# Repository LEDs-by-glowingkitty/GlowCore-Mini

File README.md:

# GlowCoreMini

## Warning:

This project is currently under active development and has not been fully tested yet. If you decide to build or clone the project, be aware the project might not work yet as expected. Use at your own risk.

## What is this project?

A small PCB for controlling one LED strip. Program the integrated ESP32, and power everything via USB-C or DC power.

## Links

- [Schematic](https://github.com/glowingkitty/GlowCoreMini/blob/main/GlowCoreMini.pdf)
- [Interactive BOM](https://htmlpreview.github.io/?https://github.com/glowingkitty/GlowCoreMini/blob/main/bom/ibom.html)
- [PCB stencils](https://github.com/glowingkitty/GlowCoreMini/blob/main/PCB%20stencils)

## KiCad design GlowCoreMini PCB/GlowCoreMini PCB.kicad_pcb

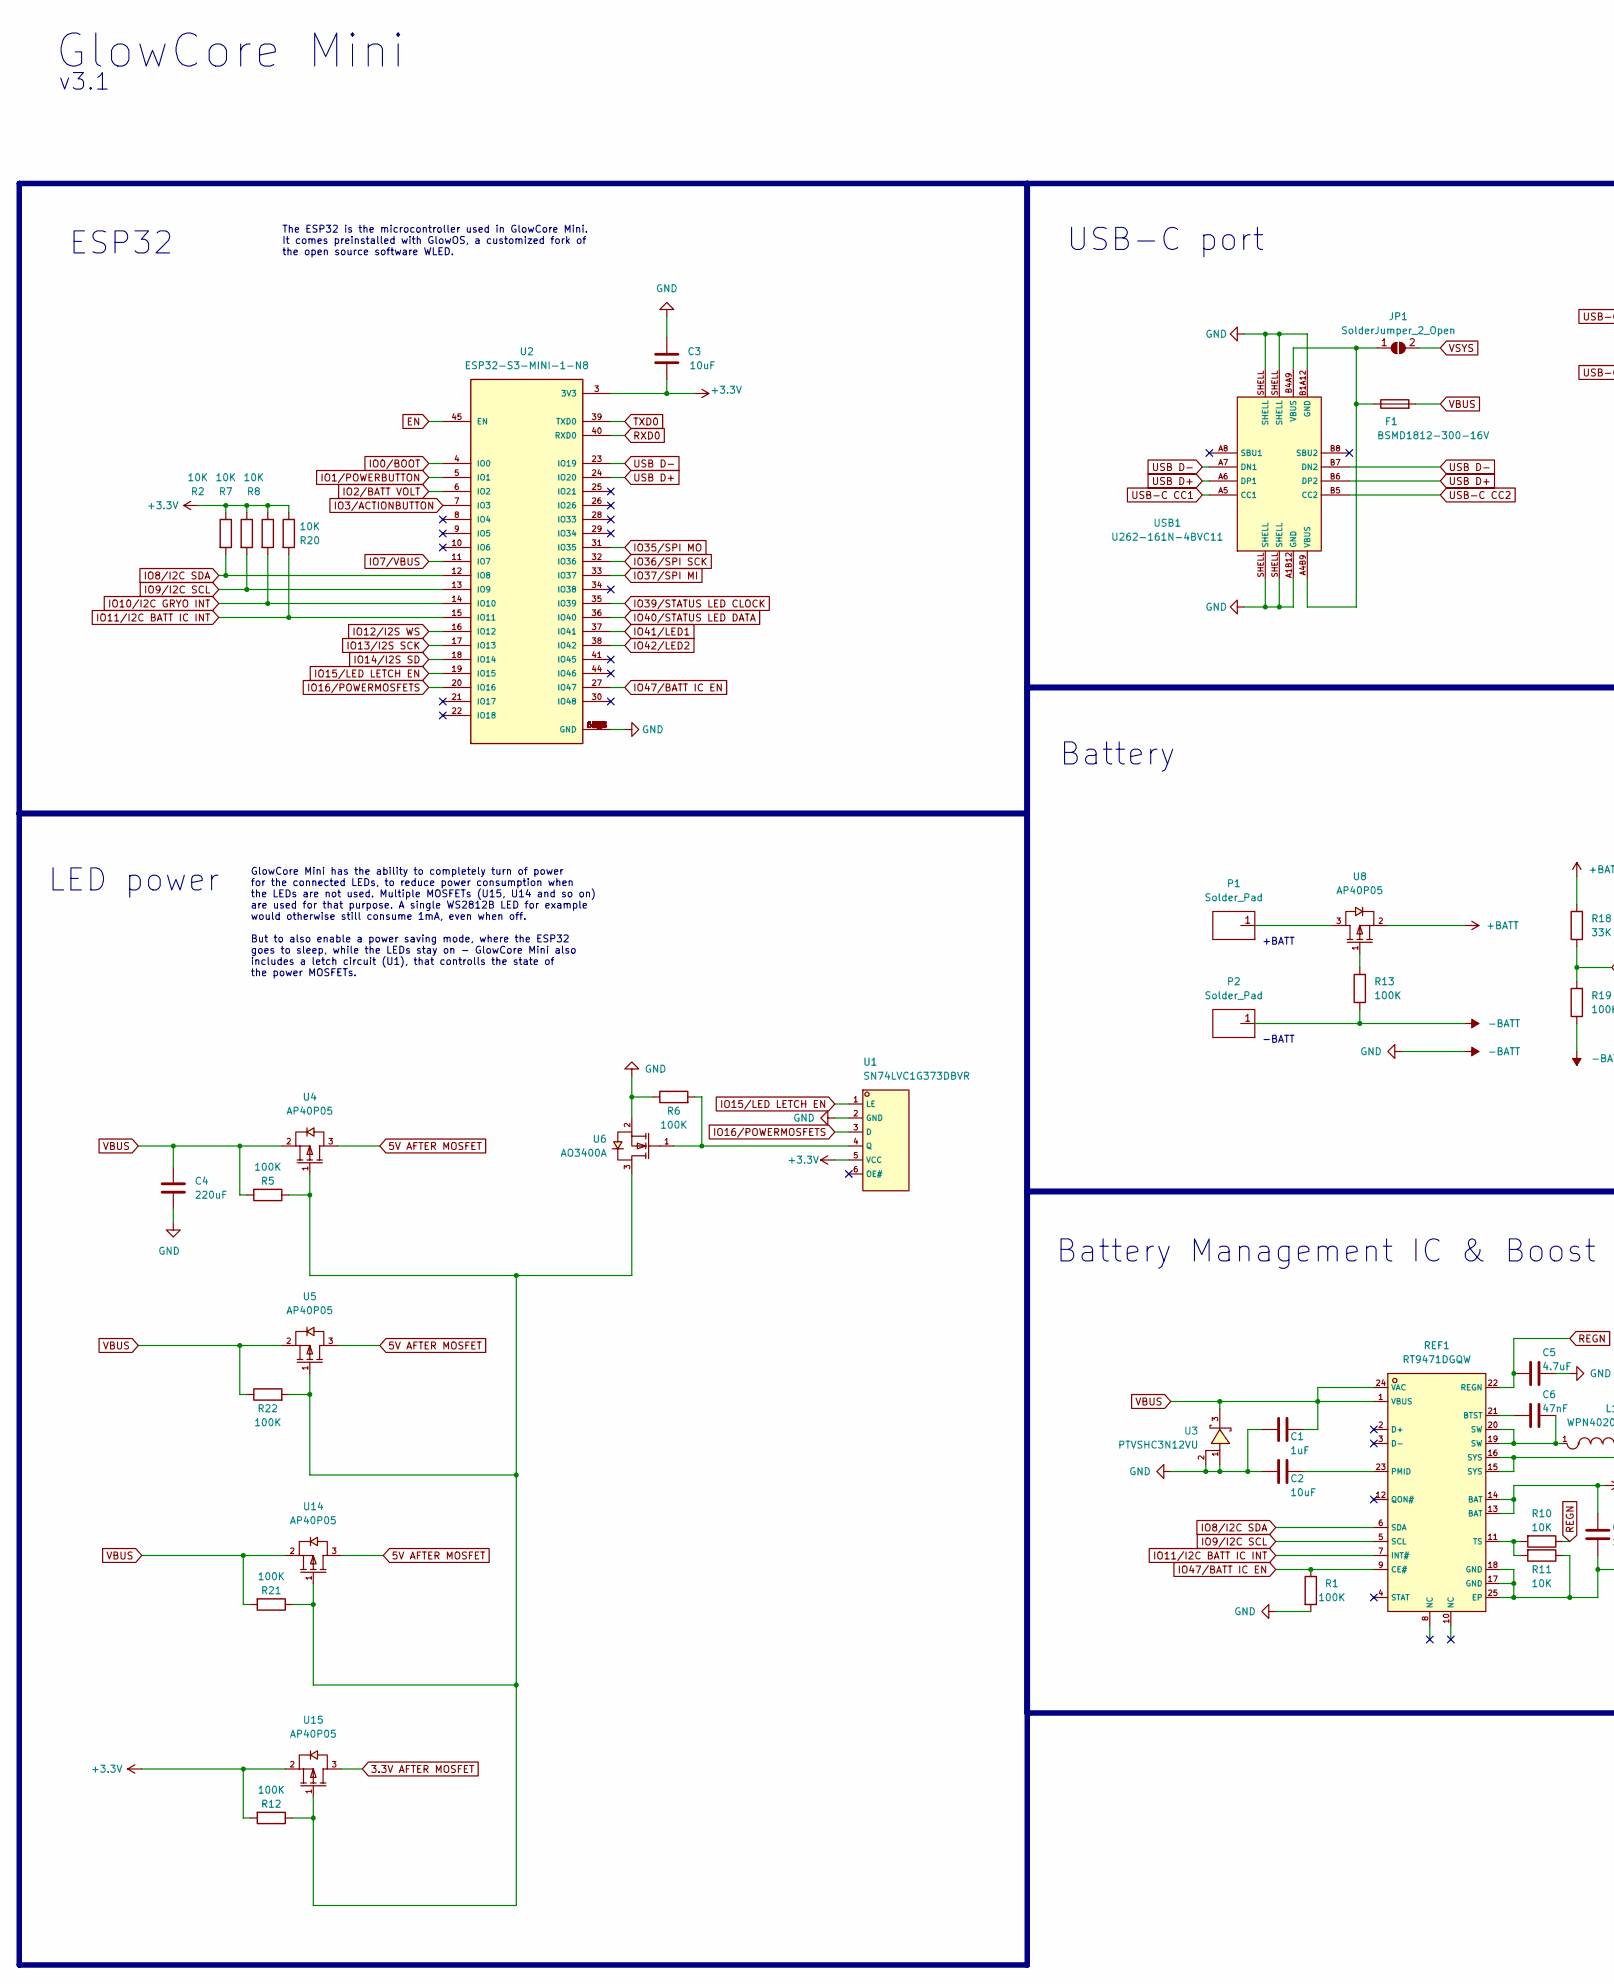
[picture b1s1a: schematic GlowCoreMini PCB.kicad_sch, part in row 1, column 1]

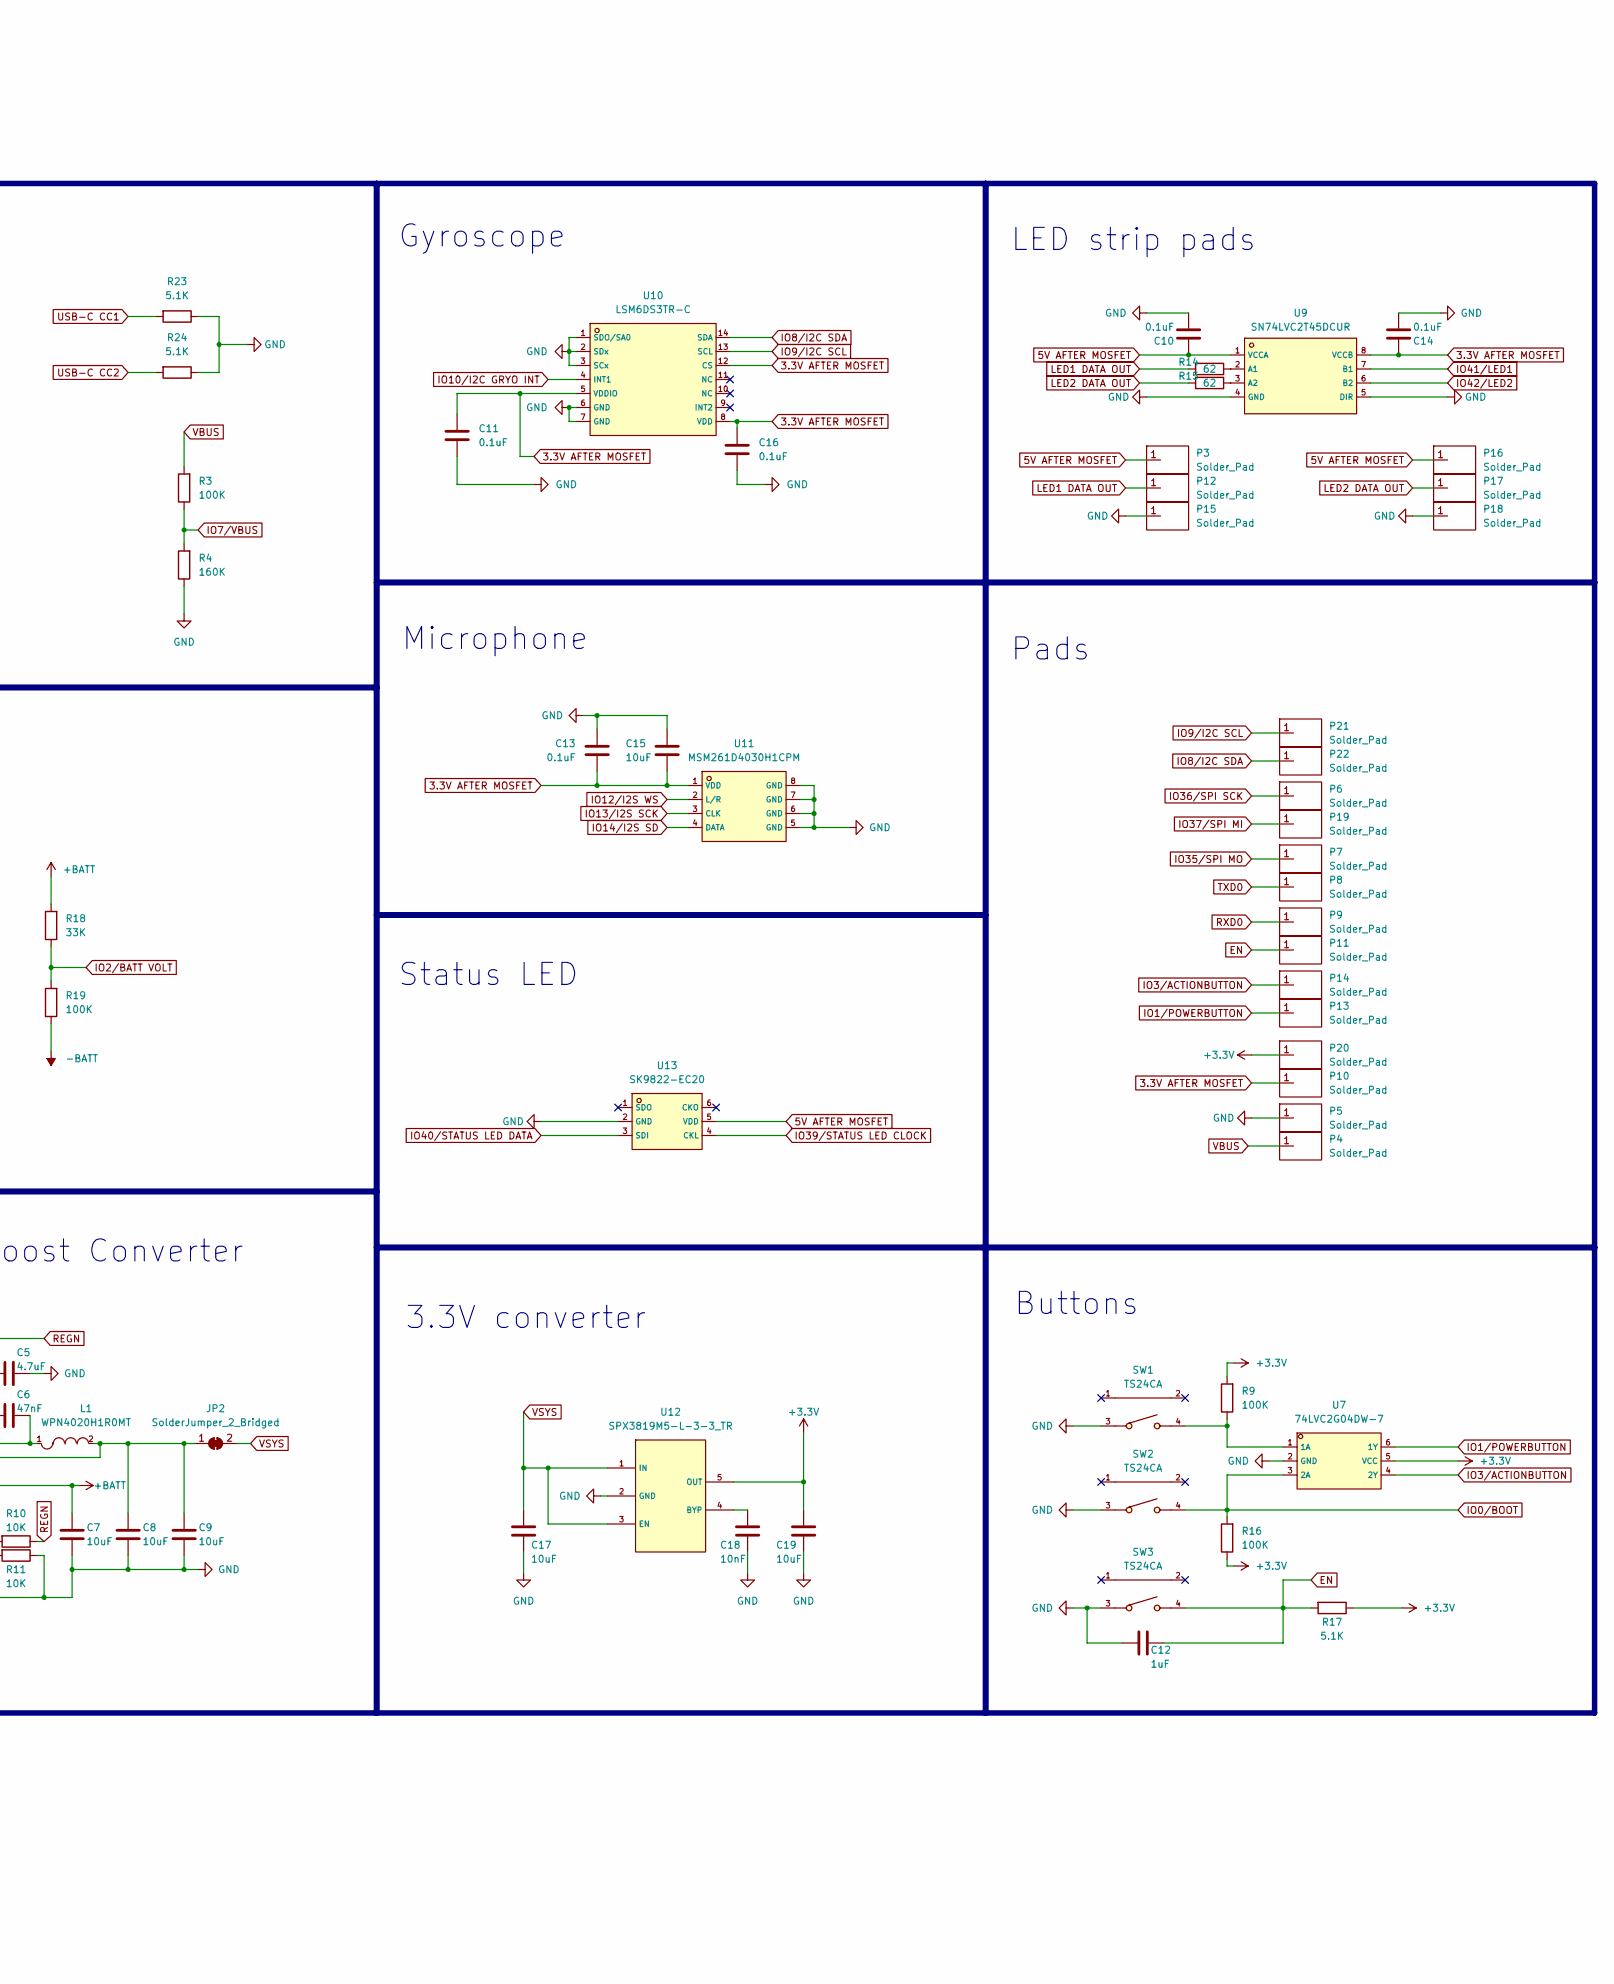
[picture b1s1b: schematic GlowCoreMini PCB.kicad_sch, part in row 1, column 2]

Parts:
C1, C12: 1uF; C_0402_1005Metric; LCSC # C52923
C2, C3, C7, C8, C9, C15, C17, C19: 10uF; C_0603_1608Metric; LCSC # C96446
C4: 220uF; C_1206_3216Metric; LCSC # C412252
C5: 4.7uF; C_0402_1005Metric; LCSC # C23733
C6: 47nF; C_0402_1005Metric; LCSC # C505502
C10, C11, C13, C14, C16: 0.1uF; C_0402_1005Metric; LCSC # C1525
C18: 10nF; C_0402_1005Metric; LCSC # C15195
F1: BSMD1812-300-16V; Fuse_1812_4532Metric_Pad1.30x3.40mm_HandSolder; LCSC # C883162
JP1: SolderJumper_2_Open; SolderJumper-2_P1.3mm_Open_RoundedPad1.0x1.5mm
JP2: SolderJumper_2_Bridged; SolderJumper-2_P1.3mm_Bridged_RoundedPad1.0x1.5mm
L1: WPN4020H1R0MT; IND-SMD_L4.0-W4.0_SLW40XX; LCSC C98359
P1, P2, P3, P4, P5, P6, P7, P8, P9, P10, P11, P12, P13, P14, P15, P16, P17, P18, P19, P20, P21, P22: Solder_Pad; Solder pad
R1, R3, R5, R6, R9, R12, R13, R16, R19, R21, R22: 100K; R_0402_1005Metric; LCSC # C25741
R2, R7, R8, R10, R11, R20: 10K; R_0402_1005Metric; LCSC # C25744
R4: 160K; R_0603_1608Metric; LCSC # C22813
R14, R15: 62; R_0402_1005Metric; LCSC # C4962
R17, R23, R24: 5.1K; R_0402_1005Metric; LCSC # C25905
R18: 33K; R_0402_1005Metric; LCSC # C25779
REF1: RT9471DGQW; RT9471_vias_in_pad; LCSC C2839437
SW1, SW2, SW3: TS24CA; SW-SMD_TS24CA; LCSC C393942
U1: SN74LVC1G373DBVR; SOT-23-6_L2.9-W1.6-P0.95-LS2.8-BR; LCSC C128413
U2: ESP32-S3-MINI-1-N8; LCSC# C2913206
U3: PTVSHC3N12VU; DFN-3_L2.0-W2.0-P1.30-BR; LCSC C110755
U4, U5, U8, U14, U15: AP40P05; SOT-23-3_L2.9-W1.3-P1.90-LS2.4-BR; LCSC # C2886385
U6: AO3400A; SOT-23-3_L2.9-W1.6-P1.90-LS2.8-BR; LCSC # C20917
U7: 74LVC2G04DW-7; SOT-363_L2.0-W1.3-P0.65-LS2.1-BR; LCSC C69053
U9: SN74LVC2T45DCUR; VSSOP-8_L2.4-W2.1-P0.50-LS3.2-BR; LCSC # C15741
U10: LSM6DS3TR-C; LGA-14_L3.0-W2.5-P0.50-TL; LCSC C967633
U11: MSM261D4030H1CPM; MIC-SMD_8P-L4.0-W3.0_ZTS6231; LCSC C966942
U12: SPX3819M5-L-3-3_TR; SOT-23-5_L3.0-W1.7-P0.95-LS2.8-BR; LCSC # C9055
U13: SK9822-EC20; LED-SMD_6P-L2.0-W2.0-P0.80-TL; LCSC C2909059
USB1: U262-161N-4BVC11; USB-3.1-SMD_U262-161N-4BVC11; LCSC # C319148

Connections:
3.3V AFTER MOSFET: C11.1, C13.2, C14.1, C15.2, C16.1, P10.1, U9.8 (VCCB), U10.5 (VDDIO), U10.8 (VDD), U10.12 (CS), U11.1 (VDD), U15.3 (D)
5V AFTER MOSFET: C10.1, P3.1, P16.1, U4.3 (D), U5.3 (D), U9.1 (VCCA), U13.5 (VDD), U14.3 (D)
+3V3: C3.2, C19.2, P20.1, R2.1, R7.1, R8.1, R9.2, R12.2, R16.1, R17.1, R20.1, U1.5 (VCC), U2.3 (3V3), U7.5 (VCC), U12.5 (OUT), U15.2 (S)
+BATT: C7.2, R18.2, REF1.13 (BAT), REF1.14 (BAT), U8.2 (S)
-BATT: C1.1, C2.1, C3.1, C4.2, C5.2, C7.1, C8.1, C9.1, C10.2, C11.2, C12.1, C13.1, C14.2, C15.1, C16.2, C17.1, C18.1, C19.1, P2.1, P5.1, P15.1, P18.1, R1.2, R4.1, R6.1, R11.1, R13.1, R19.1, R23.1, R24.1, REF1.17 (GND), REF1.18 (GND), REF1.25 (EP), SW1.3, SW2.3, SW3.3, U1.2 (GND), U2.1 (GND), U2.2 (GND), U2.42 (GND), U2.43 (GND), U2.46 (GND), U2.47 (GND), U2.48 (GND), U2.49 (GND), U2.50 (GND), U2.51 (GND), U2.52 (GND), U2.53 (GND), U2.54 (GND), U2.55 (GND), U2.56 (GND), U2.57 (GND), U2.58 (GND), U2.59 (GND), U2.60 (GND), U2.61 (GND), U2.61_1 (GND), U2.61_2 (GND), U2.61_3 (GND), U2.61_4 (GND), U2.61_5 (GND), U2.61_6 (GND), U2.61_7 (GND), U2.61_8 (GND), U2.62 (GND), U2.63 (GND), U2.64 (GND), U2.65 (GND), U3.1 (A), U3.2 (1), U6.2 (S), U7.2 (GND), U9.4 (GND), U9.5 (DIR), U10.1 (SDO/SA0), U10.2 (SDx), U10.3 (SCx), U10.6 (GND), U10.7 (GND), U11.5 (GND), U11.6 (GND), U11.7 (GND), U11.8 (GND), U12.2 (GND), U13.2 (GND), USB1.A1B12 (GND), USB1.B1A12 (GND), USB1.SHELL
EN: C12.2, P11.1, R17.2, SW3.4, U2.45 (EN)
IO0/BOOT: R16.2, SW2.4, U2.4 (IO0), U7.3 (2A)
IO1/POWERBUTTON: P13.1, U2.5 (IO1), U7.6 (1Y)
IO2/BATT VOLT: R18.1, R19.2, U2.6 (IO2)
IO3/ACTIONBUTTON: P14.1, U2.7 (IO3), U7.4 (2Y)
IO7/VBUS: R3.1, R4.2, U2.11 (IO7)
IO8/I2C SDA: P22.1, R2.2, REF1.6 (SDA), U2.12 (IO8), U10.14 (SDA)
IO9/I2C SCL: P21.1, R7.2, REF1.5 (SCL), U2.13 (IO9), U10.13 (SCL)
IO10/I2C GRYO INT: R8.2, U2.14 (IO10), U10.4 (INT1)
IO11/I2C BATT IC INT: R20.2, REF1.7 (INT#), U2.15 (IO11)
IO12/I2S WS: U2.16 (IO12), U11.2 (L/R)
IO13/I2S SCK: U2.17 (IO13), U11.3 (CLK)
IO14/I2S SD: U2.18 (IO14), U11.4 (DATA)
IO15/LED LETCH EN: U1.1 (LE), U2.19 (IO15)
IO16/POWERMOSFETS: U1.3 (D), U2.20 (IO16)
IO35/SPI MO: P7.1, U2.31 (IO35)
IO36/SPI SCK: P6.1, U2.32 (IO36)
IO37/SPI MI: P19.1, U2.33 (IO37)
IO39/STATUS LED CLOCK: U2.35 (IO39), U13.4 (CKL)
IO40/STATUS LED DATA: U2.36 (IO40), U13.3 (SDI)
IO41/LED1: U2.37 (IO41), U9.7 (B1)
IO42/LED2: U2.38 (IO42), U9.6 (B2)
IO47/BATT IC EN: R1.1, REF1.9 (CE#), U2.27 (IO47)
LED1 DATA OUT: P12.1, R14.2
LED2 DATA OUT: P17.1, R15.2
unnamed: C6.2, L1.1, REF1.19 (SW), REF1.20 (SW)
unnamed: F1.1, JP1.1 (A), USB1.A4B9 (VBUS), USB1.B4A9 (VBUS)
unnamed: C8.2, C9.2, JP2.1 (A), L1.2, REF1.15 (SYS), REF1.16 (SYS)
unnamed: C6.1, REF1.21 (BTST)
unnamed: C2.2, REF1.23 (PMID)
unnamed: R10.2, R11.2, REF1.11 (TS)
unnamed: R6.2, U1.4 (Q), U6.1 (G)
unnamed: R9.1, SW1.4, U7.1 (1A)
unnamed: P1.1, U8.3 (D)
unnamed: R13.2, U8.1 (G)
unnamed: R14.1, U9.2 (A1)
unnamed: R15.1, U9.3 (A2)
unnamed: C18.2, U12.4 (BYP)
unnamed: R5.1, R12.1, R21.1, R22.2, U4.1 (G), U5.1 (G), U6.3 (D), U14.1 (G), U15.1 (G)
REGN: C5.1, R10.1, REF1.22 (REGN)
RXD0: P9.1, U2.40 (RXD0)
TXD0: P8.1, U2.39 (TXD0)
USB D+: U2.24 (IO20), USB1.A6 (DP1), USB1.B6 (DP2)
USB D-: U2.23 (IO19), USB1.A7 (DN1), USB1.B7 (DN2)
USB-C CC1: R23.2, USB1.A5 (CC1)
USB-C CC2: R24.2, USB1.B5 (CC2)
VBUS: C1.2, C4.1, F1.2, P4.1, R3.2, R5.2, R21.2, R22.1, REF1.1 (VBUS), REF1.24 (VAC), U3.3 (K), U4.2 (S), U5.2 (S), U14.2 (S)
VSYS: C17.2, JP1.2 (B), JP2.2 (B), U12.1 (IN), U12.3 (EN)

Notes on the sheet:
3.3V converter
Buttons
LED power
LED strip pads
GlowCore Mini
The ESP32 is the microcontroller used in GlowCore Mini. It comes preinstalled with GlowOS, a customized fork of the open source software WLED.
v3.1
-BATT
+BATT
Status LED
Battery Management IC & Boost Converter
Gyroscope
Pads
USB-C port
Microphone
Battery
ESP32
GlowCore Mini has the ability to completely turn of power for the connected LEDs, to reduce power consumption when the LEDs are not used. Multiple MOSFETs (U15, U14 and so on) are used for that purpose. A single WS2812B LED for example would otherwise still consume 1mA, even when off. But to also e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

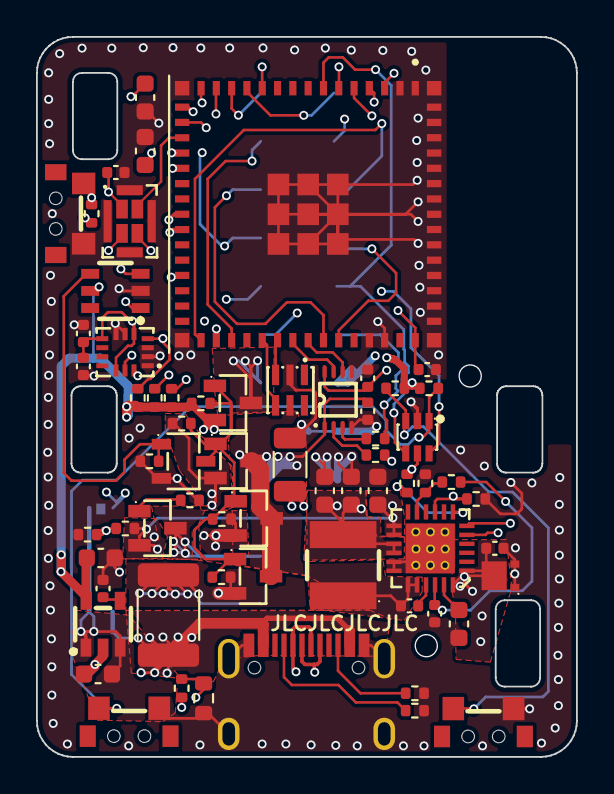
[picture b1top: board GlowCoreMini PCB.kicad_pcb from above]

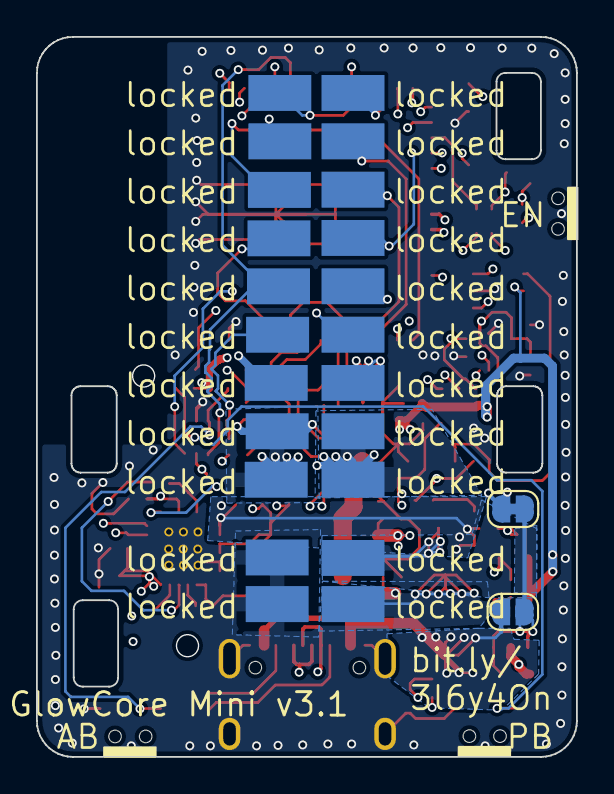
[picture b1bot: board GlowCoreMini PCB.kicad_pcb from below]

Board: 4 copper layers, 30.0 x 40.0 mm, 89 parts (24 on the bottom side), 53 nets.

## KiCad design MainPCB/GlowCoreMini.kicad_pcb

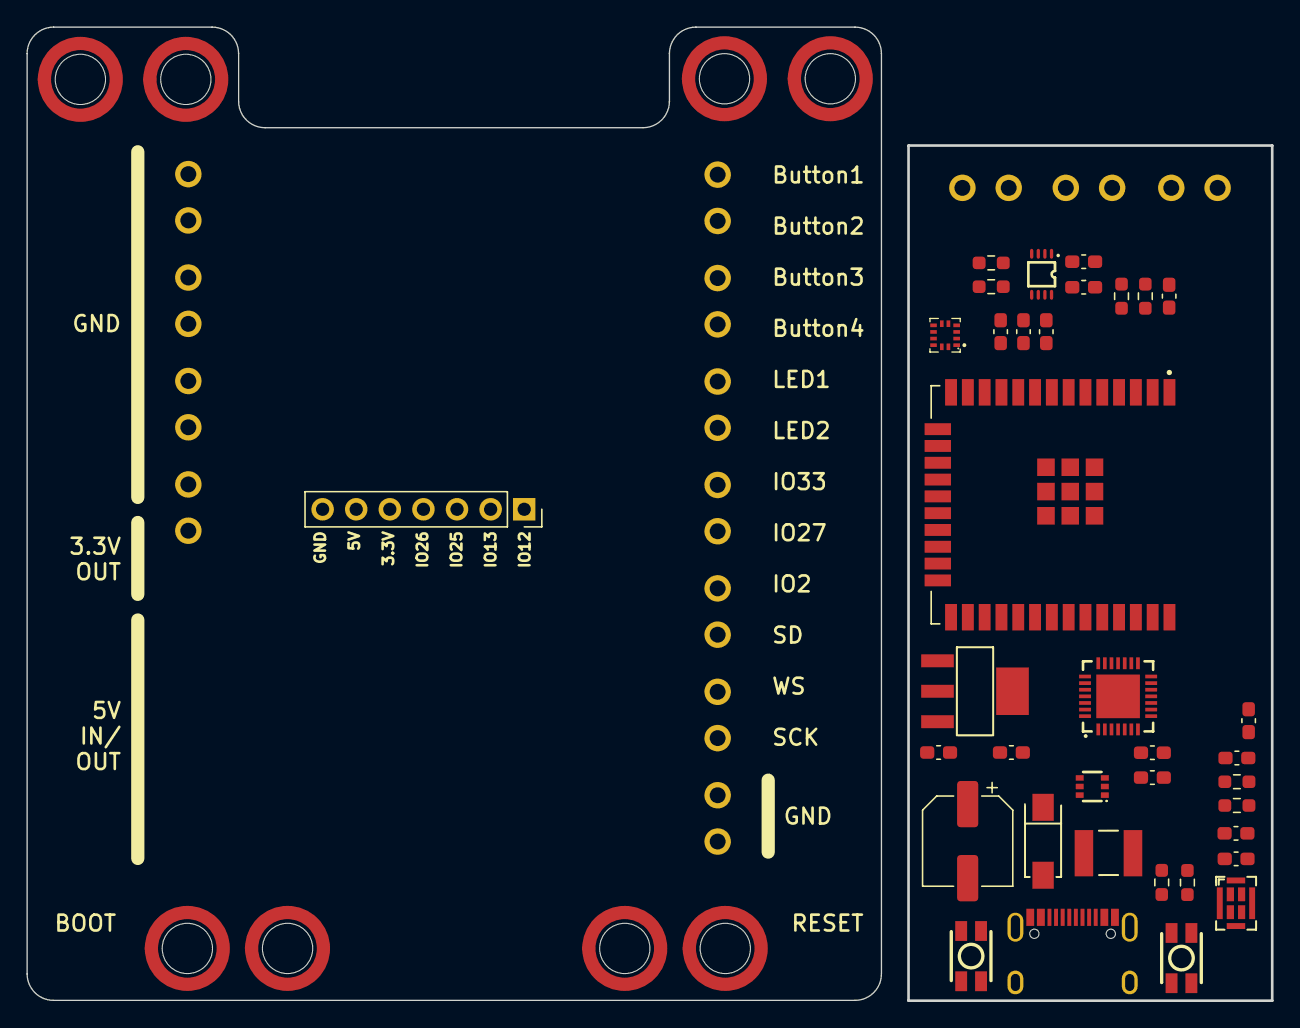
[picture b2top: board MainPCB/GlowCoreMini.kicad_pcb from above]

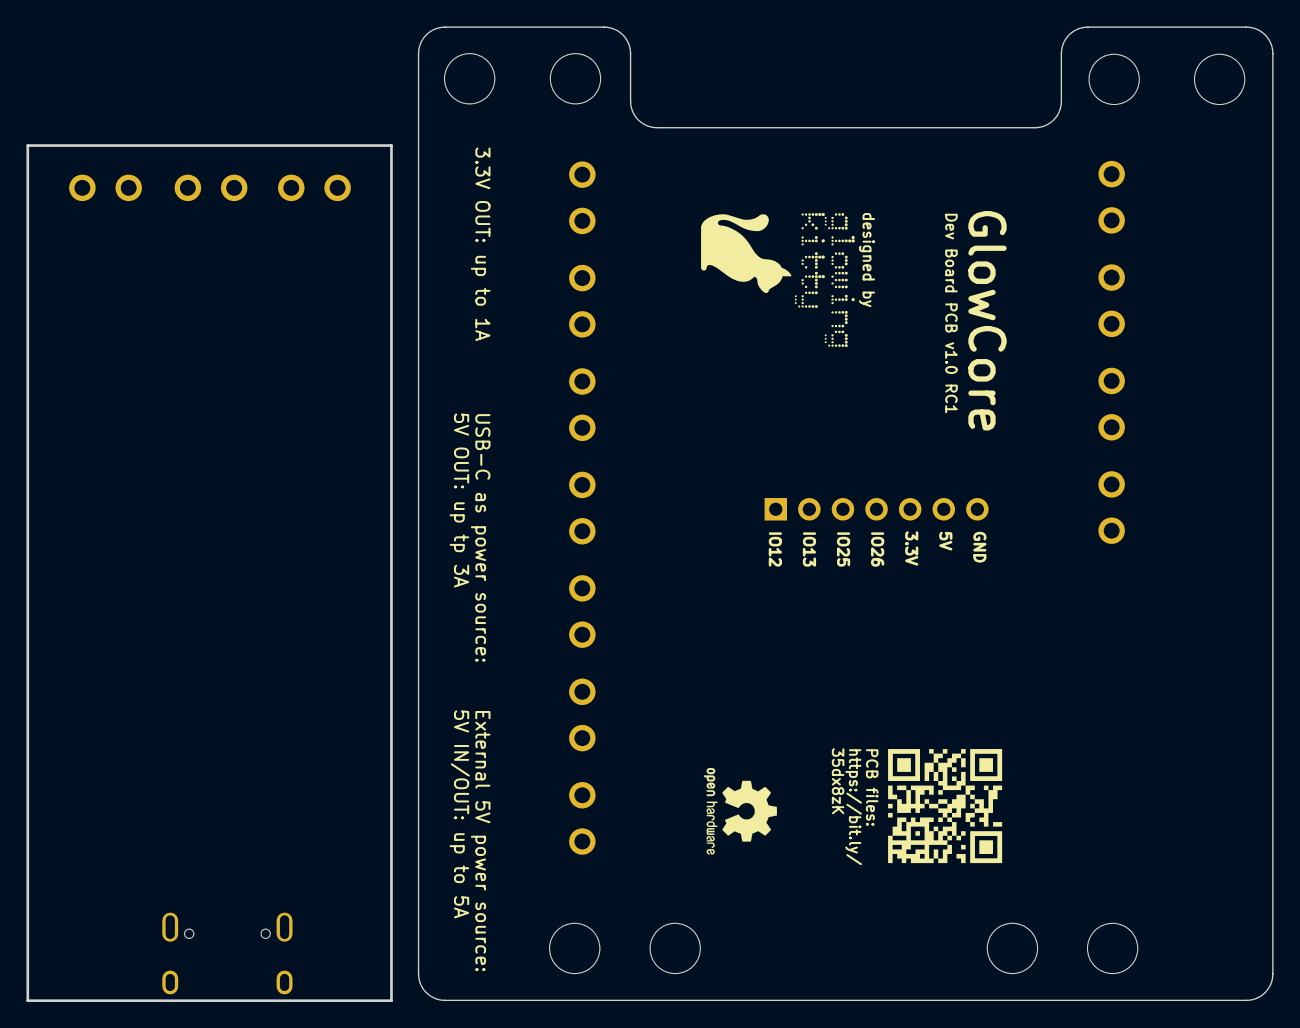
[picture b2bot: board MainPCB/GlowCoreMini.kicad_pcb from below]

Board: 2 copper layers, 94.1 x 73.6 mm, 60 parts (2 on the bottom side), 39 nets, no tracks yet.

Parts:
C1, C2, C7, C8, C12: 0.1uF; C_0603_1608Metric_Pad1.08x0.95mm_HandSolder
C3, C6, C11, C15: 10uF; C_0603_1608Metric_Pad1.08x0.95mm_HandSolder
C4: 220uF 10V; CP_Elec_6.3x5.4
C5: 4.7uF 6.3V 10%; C_0603_1608Metric_Pad1.08x0.95mm_HandSolder
C9: 10nF; C_0603_1608Metric_Pad1.08x0.95mm_HandSolder
C10: 2.2uF; C_0603_1608Metric_Pad1.08x0.95mm_HandSolder
C13, C14: 1uF; C_0603_1608Metric_Pad1.08x0.95mm_HandSolder
F1: BSMD1812-300-16V; F1812
J1: Conn_01x07; PinSocket_1x07_P2.54mm_Vertical
OSHW logo: OSHW-Logo2_7.3x6mm_SilkScreen
R1, R8: 62; R_0603_1608Metric_Pad0.98x0.95mm_HandSolder
R2, R3: 5.1K 1%; R_0603_1608Metric_Pad0.98x0.95mm_HandSolder
R4, R5: 220; R_0603_1608Metric_Pad0.98x0.95mm_HandSolder
R6, R7: 10K; R_0603_1608Metric_Pad0.98x0.95mm_HandSolder
SW1, SW2: TS-1185EC-C-D-B; SW-SMD_4P-L3.7-W3.0-P1.50-LS4.7
U1, U2, U3, U4, U30, U31, U32, U33: SMTSO3030CTJ
U7: ESP32-WROOM-32E; WIFI-SMD_ESP32-WROOM-32E
U8: SN74LVC2T45DCUR; VSSOP-8_L2.4-W2.1-P0.50-LS3.2-BR
U11: QMA7981; LGA-12_L2.0-W2.0-P0.50-BL
U12: BL1117-33CX; SOT-223-4_L6.5-W3.5-P2.30-LS7.0-BR
U13: CP2102-GMR; QFN-28_L5.0-W5.0-P0.50-BL-EP
U14: UMH3N; SC-70-6_L2.2-W1.3-P0.65-LS2.1-BR
U15: locked; MIC-SMD_8P-L3.0-W4.0-P0.85-BL
U16, U17, U18, U19, U20, U21, U22, U23, U24, U25, U26, U27, U28, U29: KF350-3_5-2P; CONN-TH_P3.50_KF350-3.5-2P
U34: SS54; SMA_L4.4-W2.8-LS5.4-RD
USB1: U262-161N-4BVC11; USB-3.1-SMD_U262-161N-4BVC11
logo: LOGO

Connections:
+3V3: C2.1, C3.2, C5.2, C7.1, C8.1, C9.1, C10.1, C11.2, C12.2, C15.2, J1.5, R6.2, R7.2, U7.2 (3V3), U8.8 (VCCB), U11.3 (VDD_IO), U11.7 (VDD), U12.2 (Vout), U12.4 (Vout), U13.6 (VDD), U13.7 (REGIN), U15.1 (VDD), U18.1, U19.2
+5V: C1.1, C4.1, C6.2, J1.6, U8.1 (VCCA), U12.3 (Vin), U16.1, U16.2, U17.1, U17.2, U18.2, U34.1 (K)
DTR: U13.28 (DTR), U14.2 (B), U14.4 (E)
GND: C1.2, C2.2, C3.1, C4.2, C5.1, C6.1, C7.2, C8.2, C9.2, C10.2, C11.1, C12.1, C13.2, C14.2, C15.1, J1.7, R2.1, R3.1, SW1.1, SW2.1, U7.1 (GND), U7.15 (GND), U7.38 (GND), U7.39 (GND), U8.4 (GND), U8.5 (DIR), U11.4 (RES_V1), U11.8 (GND_IO), U11.9 (GND), U12.1 (GND), U13.3 (GND), U13.29 (GND_PAD), U15.5 (GND), U15.6 (GND), U15.7 (GND), U15.8 (GND), U19.1, U20.1, U20.2, U21.1, U21.2, U22.1, U22.2, U23.1, U23.2, USB1.A1B12 (GND), USB1.B1A12 (GND), USB1.SHELL
IO0: C14.1, R5.2, R7.1, U7.25 (IO0), U14.3 (C)
IO2: U7.24 (IO2), U25.2
IO12/MISO: J1.1, U7.14 (IO12), U11.2 (SDX)
IO13/MOSI: J1.2, U7.16 (IO13), U11.1 (AD0)
IO14/SCK: U7.13 (IO14), U11.12 (SCX), U15.3 (CLK), U24.1
IO15/WS: U7.23 (IO15), U11.10 (SEN_B), U15.2 (L/R), U24.2
IO16/LED1: U7.27 (IO16), U8.7 (B1)
IO17/LED2: U7.28 (IO17), U8.6 (B2)
IO21/INT1: U7.33 (IO21), U11.5 (INT1)
IO22/INT2: U7.36 (IO22), U11.6 (INT2)
IO25/A1/DAC1: J1.3, U7.10 (IO25)
IO26/A0/DAC2: J1.4, U7.11 (IO26)
IO27: U7.12 (IO27), U26.1
IO32/SD: U7.8 (IO32), U15.4 (DATA), U25.1
IO33: U7.9 (IO33), U26.2
IO34/BUTTON3: U7.6 (I34), U28.2
IO35/BUTTON4: U7.7 (I35), U28.1
IO36/BUTTON1: U7.4 (SENSOR_VP), U29.2
IO39/BUTTON2: U7.5 (SENSOR_VN), U29.1
LED1 DATA OUT: R1.2, U27.2
LED2 DATA OUT: R8.2, U27.1
unnamed: F1.2, U34.2 (A)
unnamed: R1.1, U8.2 (A1)
unnamed: R4.1, SW1.2
unnamed: R5.1, SW2.2
unnamed: R8.1, U8.3 (A2)
RESET: C13.1, R4.2, R6.1, U7.3 (EN), U14.6 (C)
RTS: U13.24 (RTS), U14.1 (E), U14.5 (B)
RXD0: U7.34 (RXD0), U13.26 (TXD)
TXD0: U7.35 (TXD0), U13.25 (RXD)
USB-C CC1: R2.2, USB1.A5 (CC1)
USB-C CC2: R3.2, USB1.B5 (CC2)
USB-C DATA+: U13.4 (D+), USB1.A6 (DP1), USB1.B6 (DP2)
USB-C DATA-: U13.5 (D-), USB1.A7 (DN1), USB1.B7 (DN2)
VBUS: F1.1, U13.8 (VBUS), USB1.A4B9 (VBUS), USB1.B4A9 (VBUS)

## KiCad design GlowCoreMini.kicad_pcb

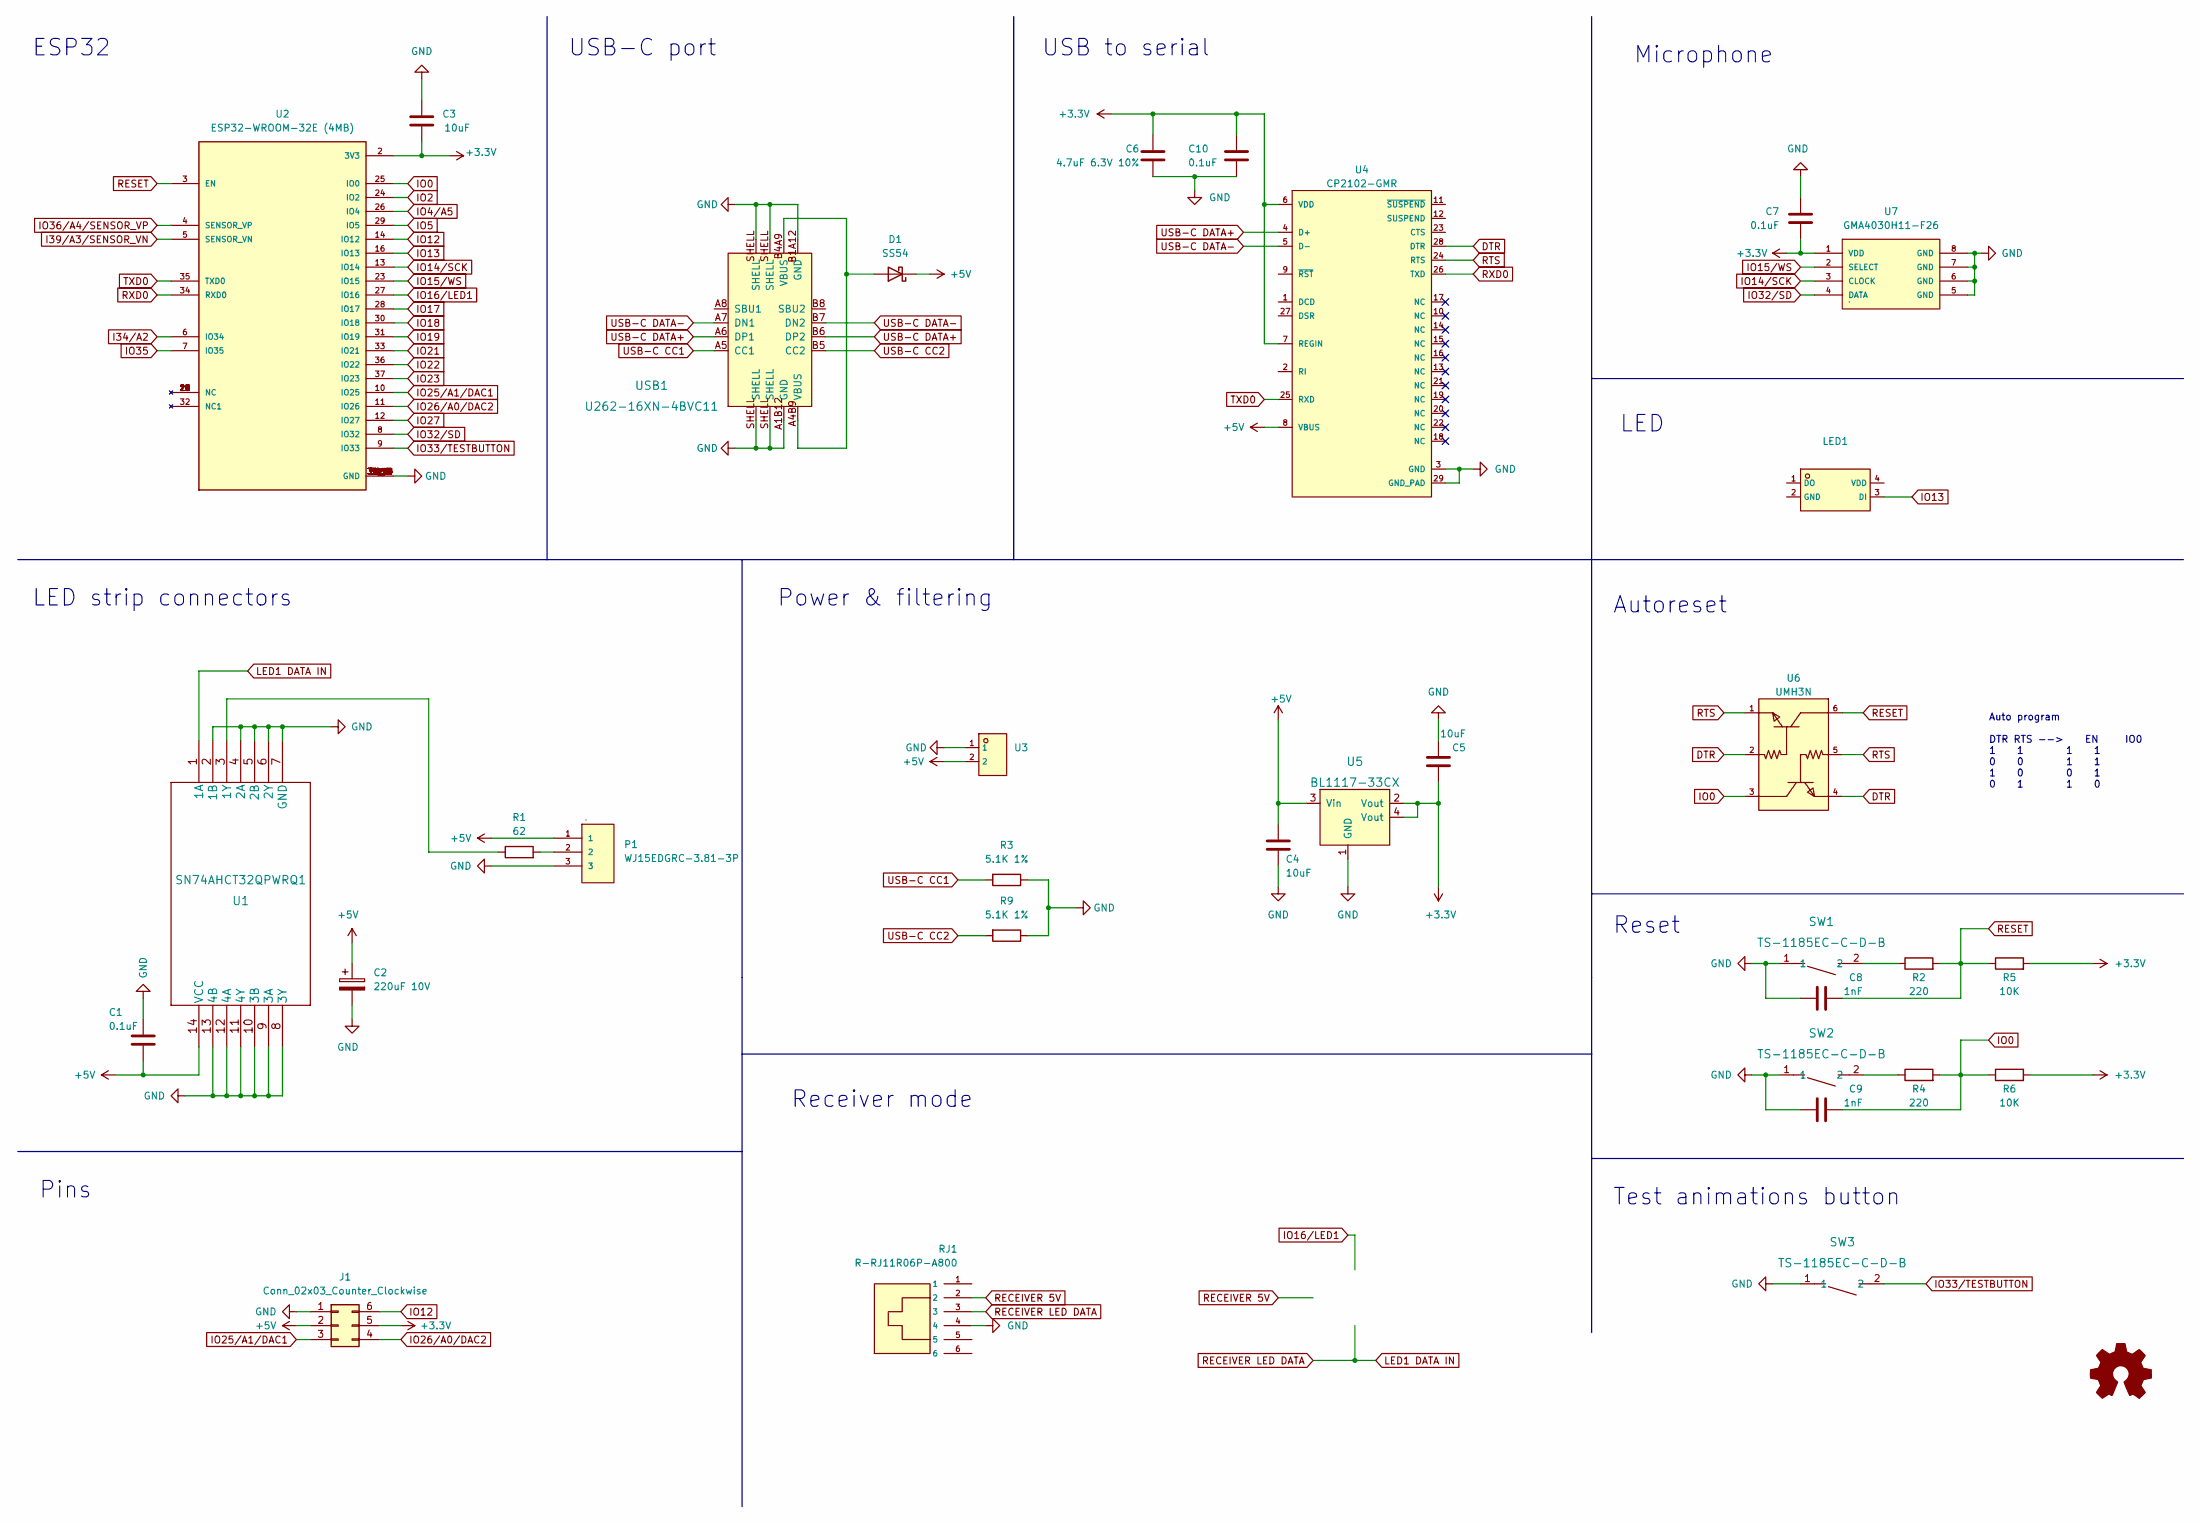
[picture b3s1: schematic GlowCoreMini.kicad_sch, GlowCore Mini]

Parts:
C1, C7, C10: 0.1uF; C_0603_1608Metric_Pad1.08x0.95mm_HandSolder; Mfr. Part # 06035C104K4Z2A; LCSC Part # C597194
C2: 220uF 10V; CP_Elec_6.3x5.4; Mfr. Part # RT1A221M0605; LCSC Part # C267466
C3, C4, C5: 10uF; C_0603_1608Metric_Pad1.08x0.95mm_HandSolder; Mfr. Part # C0603X5R106K250NT; LCSC Part # C729457
C6: 4.7uF 6.3V 10%; C_0603_1608Metric_Pad1.08x0.95mm_HandSolder
C8, C9: 1nF; C_0603_1608Metric_Pad1.08x0.95mm_HandSolder; Mfr. Part # C0603X5R106K250NT; LCSC Part # C729457
D1: SS54; D_SMA
J1: Conn_02x03_Counter_Clockwise; PinSocket_2x03_P2.54mm_Vertical
LED1: (no value)
P1: WJ15EDGRC-3.81-3P
R1: 62; R_0603_1608Metric_Pad0.98x0.95mm_HandSolder; Mfr. Part # RCT0362RJLF; LCSC Part # C177352
R2, R4: 220; R_0603_1608Metric_Pad0.98x0.95mm_HandSolder; Mfr. Part # RC0603FR-0710KL; LCSC Part # C98220
R3, R9: 5.1K 1%; R_0603_1608Metric_Pad0.98x0.95mm_HandSolder; Mfr. Part # HPCR0603F5K10K9; LCSC Part # C365193
R5, R6: 10K; R_0603_1608Metric_Pad0.98x0.95mm_HandSolder; Mfr. Part # RC0603FR-0710KL; LCSC Part # C98220
RJ1: R-RJ11R06P-A800
SW1, SW2, SW3: TS-1185EC-C-D-B; Mfr. Part # TS-1185EC-C-D-B; LCSC Part # C318893
U1: SN74AHCT32QPWRQ1; Mfr. Part # SN74AHCT32QPWRQ1; LCSC Part # C507218
U2: ESP32-WROOM-32E (4MB); MODULE_ESP32-WROOM-32E_(16MB); Mfr. Part # ESP32-WROOM-32E(4MB); LCSC Part # C701341
U3: (no value)
U4: CP2102-GMR; mouser part number 634-CP2102-GMR; digikey description USB Bridge, USB to UART USB 2.0 UART In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
U5: BL1117-33CX; SOT-223; Mfr. Part # BL1117-33CX; LCSC Part # C5400
U6: UMH3N; SC-70-6_L2.2-W1.3-P0.65-LS2.1-BR
U7: GMA4030H11-F26
USB1: U262-16XN-4BVC11; USB-3.1-SMD_U262-161N-4BVC11; Mfr. Part # U262-161N-4BVC11; LCSC Part # C319148

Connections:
+3V3: C3.2, C5.2, C6.2, C7.2, C10.1, J1.5, R5.2, R6.2, U2.2 (3V3), U4.6 (VDD), U4.7 (REGIN), U5.2 (Vout), U5.4 (Vout), U7.1 (VDD)
+5V: C1.2, C2.1, C4.2, D1.1 (K), J1.2, P1.1, U1.14 (VCC), U3.2, U4.8 (VBUS), U5.3 (Vin)
DTR: U4.28 (DTR), U6.2 (B), U6.4 (E)
GND: C1.1, C2.2, C3.1, C4.1, C5.1, C6.1, C7.1, C8.2, C9.2, C10.2, J1.1, P1.3, R3.1, R9.1, RJ1.4, SW1.1, SW2.1, SW3.1, U1.2 (1B), U1.4 (2A), U1.5 (2B), U1.6 (2Y), U1.7 (GND), U1.8 (3Y), U1.9 (3A), U1.10 (3B), U1.11 (4Y), U1.12 (4A), U1.13 (4B), U2.1 (GND), U2.15 (GND), U2.38 (GND), U2.39_1 (GND), U2.39_2 (GND), U2.39_3 (GND), U2.39_4 (GND), U2.39_5 (GND), U2.39_6 (GND), U2.39_7 (GND), U2.39_8 (GND), U2.39_9 (GND), U2.39_10 (GND), U2.39_11 (GND), U2.39_12 (GND), U2.39_13 (GND), U2.39_14 (GND), U2.39_15 (GND), U2.39_16 (GND), U2.39_17 (GND), U2.39_18 (GND), U2.39_19 (GND), U2.39_20 (GND), U2.39_21 (GND), U3.1, U4.3 (GND), U4.29 (GND_PAD), U5.1 (GND), U7.5 (GND), U7.6 (GND), U7.7 (GND), U7.8 (GND), USB1.A1B12 (GND), USB1.B1A12 (GND), USB1.SHELL
I34/A2: U2.6 (IO34)
I39/A3/SENSOR_VN: U2.5 (SENSOR_VN)
IO0: C9.1, R4.2, R6.1, U2.25 (IO0), U6.3 (C)
IO2: U2.24 (IO2)
IO4/A5: U2.26 (IO4)
IO5: U2.29 (IO5)
IO12: J1.6, U2.14 (IO12)
IO13: LED1.3 (DI), U2.16 (IO13)
IO14/SCK: U2.13 (IO14), U7.3 (CLOCK)
IO15/WS: U2.23 (IO15), U7.2 (SELECT)
IO16/LED1: U2.27 (IO16)
IO17: U2.28 (IO17)
IO18: U2.30 (IO18)
IO19: U2.31 (IO19)
IO21: U2.33 (IO21)
IO22: U2.36 (IO22)
IO23: U2.37 (IO23)
IO25/A1/DAC1: J1.3, U2.10 (IO25)
IO26/A0/DAC2: J1.4, U2.11 (IO26)
IO27: U2.12 (IO27)
IO32/SD: U2.8 (IO32), U7.4 (DATA)
IO33/TESTBUTTON: SW3.2, U2.9 (IO33)
IO35: U2.7 (IO35)
IO36/A4/SENSOR_VP: U2.4 (SENSOR_VP)
LED1 DATA IN: RJ1.3, U1.1 (1A)
unnamed: D1.2 (A), USB1.A4B9 (VBUS), USB1.B4A9 (VBUS)
unnamed: P1.2, R1.2
unnamed: R1.1, U1.3 (1Y)
unnamed: R2.1, SW1.2
unnamed: R4.1, SW2.2
RECEIVER 5V: RJ1.2
RESET: C8.1, R2.2, R5.1, U2.3 (EN), U6.6 (C)
RTS: U4.24 (RTS), U6.1 (E), U6.5 (B)
RXD0: U2.34 (RXD0), U4.26 (TXD)
TXD0: U2.35 (TXD0), U4.25 (RXD)
USB-C CC1: R3.2, USB1.A5 (CC1)
USB-C CC2: R9.2, USB1.B5 (CC2)
USB-C DATA+: U4.4 (D+), USB1.A6 (DP1), USB1.B6 (DP2)
USB-C DATA-: U4.5 (D-), USB1.A7 (DN1), USB1.B7 (DN2)

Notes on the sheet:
Microphone
Auto program DTR RTS --> EN IO0 1 1 1 1 0 0 1 1 1 0 0 1 0 1 1 0
ESP32
Power & filtering
Pins
LED
Reset
Test animations button
LED strip connectors
Autoreset
Receiver mode
USB-C port
USB to serial

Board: 2 copper layers, 33 parts (0 on the bottom side), 27 nets, no tracks yet.

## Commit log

2022-01-27 added first PCB design (still in development)
2022-01-27 added updated design (in development)
2022-01-27 added schematic and pcb pdf preview
2022-01-27 updated gitignore
2022-02-01 updated pcb design (still in dev)
2022-02-03 last fixes to prototype v1
2022-02-03 added images to readme
2022-02-03 clean up
2022-02-21 update design
2022-02-25 work on updated pcb design
2022-03-03 access ibom via github pages
2022-03-03 rename folder
2022-03-03 move ibom file back again
2022-03-13 added GlowCore Mini dev board v1.0 beta 1
2022-03-14 update images to latest pcb design
2022-03-14 add link to interactive bom
2022-03-14 added schematic link
2022-03-14 link to preview of pdf
2022-03-14 remove preview, link to github instead
2022-03-14 added 3d printable stencil
2022-03-25 added PCB stencils
2022-03-25 fixed link
2022-05-01 Create LICENSE
2022-05-06 add warning info
2022-08-24 started redesign
2022-11-16 redesigned GlowCore Mini
2022-11-17 fixed via in ground pad
2022-11-18 added status led
2022-12-03 added pinout and case test mold
2022-12-04 updated pinout naming
2022-12-04 added pinout legend
2022-12-05 updated pinout
2022-12-06 added pdf qr code to pinout
2022-12-08 updated documents
2022-12-08 updated quickstart
2022-12-14 updated 3D printed case design
2023-02-03 continued redesign of pcb
2023-02-05 split up schematic
2023-02-10 updated pcb design
2023-02-21 updated pcb

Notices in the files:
parts and their libraries:
Copyright 2021 Accelerated Designs. All rights reserved.
